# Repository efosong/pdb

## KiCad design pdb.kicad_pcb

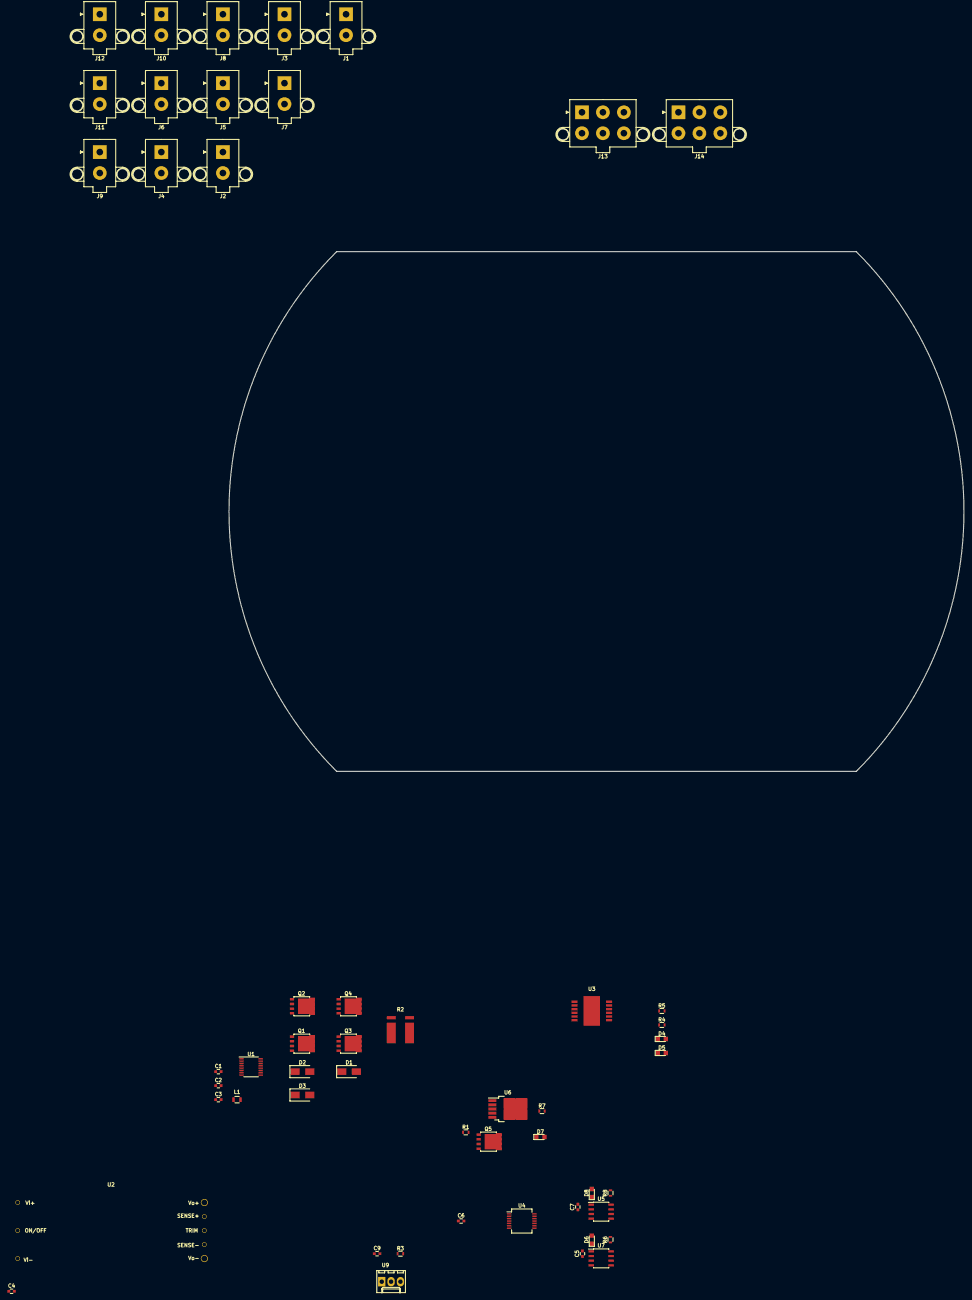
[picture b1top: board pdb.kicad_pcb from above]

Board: 2 copper layers, 200.0 x 141.4 mm, 52 parts (0 on the bottom side), 34 nets, no tracks yet.

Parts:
C1: 47n; C_0603
C2, C3: 1μ; C_0603
C4: 100μ; C_0603
C5, C6, C7, C9: 0.1μ; C_0603
D1, D2, D3: 50V; D_SMA
D4, D5, D6, D7, D8: LED; LED_0805
J1, J2, J3, J4, J5, J6, J7, J8, J9, J10, J11, J12: CONN_02X01; Molex_MegaFit_2x01x5.70mm_Straight
J13, J14: CONN_02x03; Molex_MegaFit_2x03x5.70mm_Straight
L1: 1m; L_0805
Q1, Q2, Q3, Q4: Q_NMOS_SSSGD; SOT-669_LFPAK
Q5: Q_NMOS_DGS; SOT-669_LFPAK
R1: 100; R_0603
R2: 0.002; WSLP2726
R3, R4, R5, R7: 10k; R_0603
R6, R8: 1k5; R_0603
U1: LTC1473; SSOP-16_3.9x4.9mm_Pitch0.635mm
U2: EHHD015A0A
U3: ITS5215L; DSO-12-9
U4: 74HC14; SSOP-14_5.3x6.2mm_Pitch0.65mm
U5, U7: TPS2024D; SOIC-8_3.9x4.9mm_Pitch1.27mm
U6: BTS6133D; TO-252-5_TabPin3
U9: A1120; Molex_KK-6410-03_03x2.54mm_Straight

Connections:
/Input Power Switch/PWR_IN_1: D1.2, J13.2, J13.4, J13.6, Q1.5
/Input Power Switch/PWR_IN_2: D2.2, J14.2, J14.4, J14.6, Q3.5
/Power Switch Bank/5V Power Switch A/PWR_OUT: J9.1, J10.1, R6.1, U7.6, U7.7, U7.8
/Power Switch Bank/5V Power Switch B/PWR_OUT: J11.1, J12.1, R8.1, U5.6, U5.7, U5.8
/Power Switch Bank/BAT_PWR_IN: C4.1, R2.1, U2.3, U6.3
/Power Switch Bank/Dual Power Switch/PWR_IN: U3.6, U3.12, U3.13
/Power Switch Bank/Dual Power Switch/PWR_OUT_1: D4.2, J7.1, U3.10
/Power Switch Bank/Dual Power Switch/PWR_OUT_2: D5.2, J8.1, U3.8
/Power Switch Bank/ENABLE: Q5.2, R3.2, U3.2, U3.4, U4.1, U4.13, U9.2
/Power Switch Bank/High Power Switch/PWR_OUT: J1.1, J2.1, J3.1, J4.1, J5.1, J6.1, R7.1, U6.1, U6.5
GND: C1.2, C2.2, C3.2, C4.2, C5.2, C6.2, C7.2, C9.2, D3.2, D6.1, D7.1, D8.1, J1.2, J2.2, J3.2, J4.2, J5.2, J6.2, J7.2, J8.2, J9.2, J10.2, J11.2, J12.2, Q5.3, R4.2, R5.2, U1.1, U1.2, U1.3, U1.8, U2.1, U2.2, U2.4, U2.5, U3.1, U4.3, U4.5, U4.7, U4.9, U4.11, U5.1, U7.1, U9.3
unnamed: C1.1, U1.4
unnamed: C2.1, U1.6
unnamed: C3.1, D1.1, D2.1, D3.1, L1.1, U1.5
unnamed: D4.1, R4.1
unnamed: D5.1, R5.1
unnamed: D6.2, R6.2
unnamed: D7.2, R7.2
unnamed: D8.2, R8.2
unnamed: L1.2, U1.7
unnamed: Q1.1, Q1.2, Q1.3, Q2.1, Q2.2, Q2.3, U1.15
unnamed: Q1.4, U1.16
unnamed: Q2.4, U1.14
unnamed: Q2.5, Q4.5, R2.4
unnamed: Q3.1, Q3.2, Q3.3, Q4.1, Q4.2, Q4.3, U1.10
unnamed: Q3.4, U1.11
unnamed: Q4.4, U1.9
unnamed: Q5.1, R1.2
unnamed: R1.1, U6.2
unnamed: R2.2, U1.12
unnamed: R2.3, U1.13
unnamed: U4.2, U7.4
unnamed: U4.12, U5.4
VCC: C5.1, C6.1, C7.1, C9.1, R3.1, U2.7, U2.8, U4.14, U5.2, U5.3, U7.2, U7.3, U9.1

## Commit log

2017-07-01 create blank kicad project
2017-07-02 add overall hierarchical layout
2017-07-02 add datasheets folder
2017-07-02 add input power switching circuit
2017-07-02 add 5v regulator
2017-07-02 add value to 5v regulator decoupling cap
2017-07-02 add killswitch
2017-07-08 add dual power switch
2017-07-08 add 5v power switch
2017-07-08 add high power switch
2017-07-09 clean up
2017-07-09 power switches connect to pgnd
2017-07-09 more cleaning
2017-07-09 update title box
2017-07-09 clean up after annotate
2017-07-09 fix resistor value
2017-07-09 fix broken annotation
2017-07-09 fix issue with incorrect symbol
2017-07-09 fix unconnected pin on transistor
2017-07-09 fix unconnected pin on (another) transistor
2017-07-09 add nc marker to pin
2017-07-09 fix pin based errors
2017-07-09 add datasheet for 74HC14D
2017-07-09 add connectors for batteries
2017-07-09 minor changes
2017-07-09 fix reference of resistor (again...)
2017-07-15 add LEDs to indicate switch condition; fix hierarchical sheet issues
2017-07-16 assign footprints to components
2017-07-22 basic pcb setup
